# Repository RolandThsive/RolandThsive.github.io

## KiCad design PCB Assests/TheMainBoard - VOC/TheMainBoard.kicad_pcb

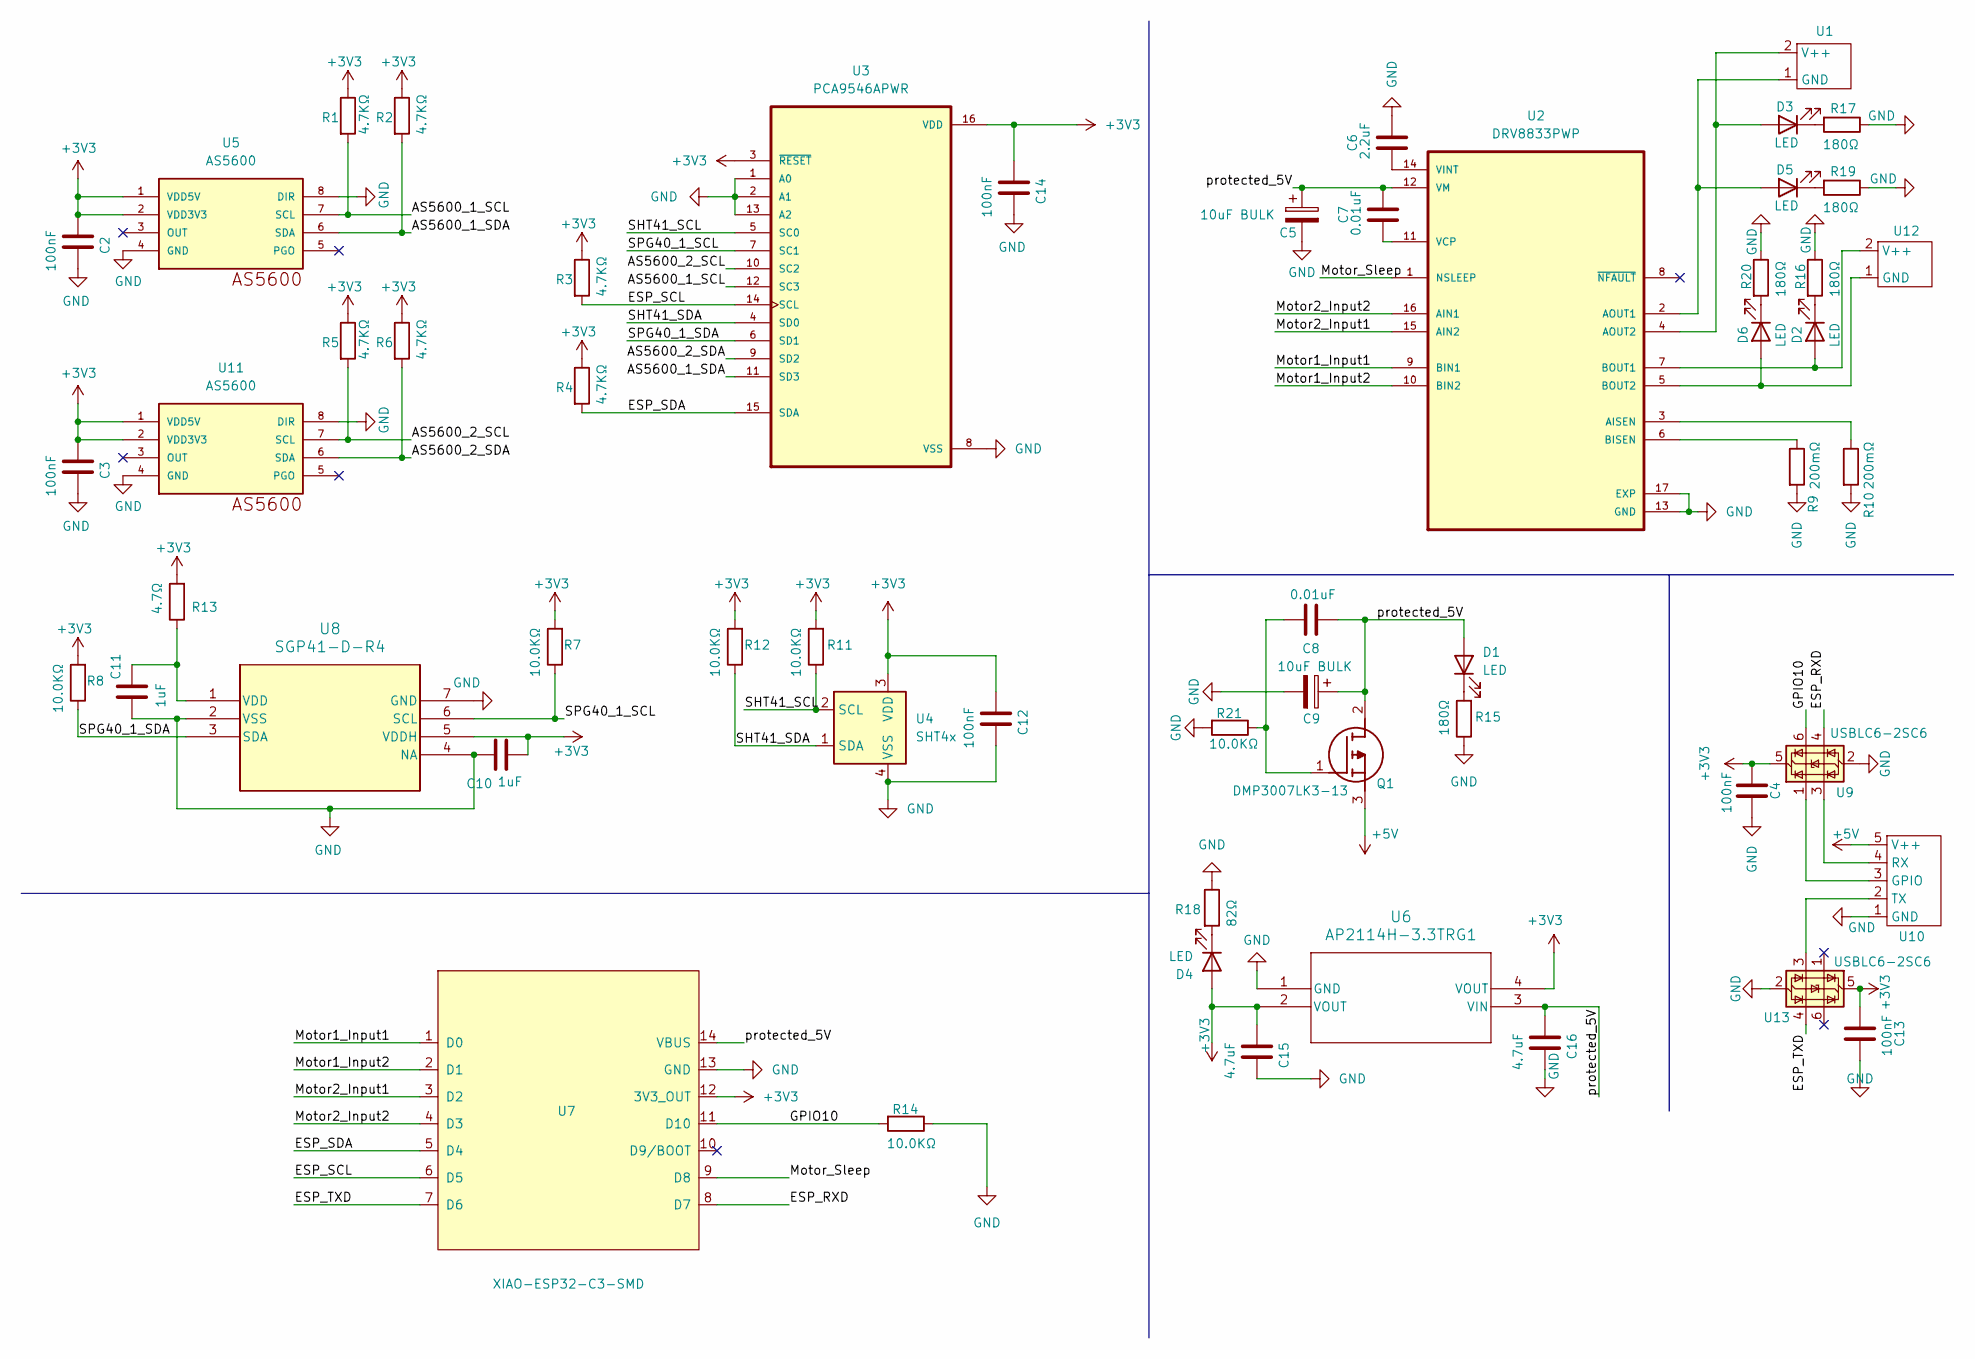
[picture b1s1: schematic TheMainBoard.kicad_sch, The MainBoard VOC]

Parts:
C2, C3, C4, C12, C13, C14: 100nF; C_0805_2012Metric_Pad1.18x1.45mm_HandSolder
C5, C9: 10uF BULK; CP_EIA-3528-21_Kemet-B_HandSolder
C6: 2.2uF; C_0805_2012Metric_Pad1.18x1.45mm_HandSolder
C7, C8: 0.01uF; C_0805_2012Metric_Pad1.18x1.45mm_HandSolder
C10, C11: 1uF; C_0805_2012Metric_Pad1.18x1.45mm_HandSolder
C15, C16: 4.7uF; C_0805_2012Metric_Pad1.18x1.45mm_HandSolder
D1, D2, D3, D4, D5, D6: LED; LED_1206_3216Metric
Q1: DMP3007LK3-13; DMP3007LK313; Manufacturer_Part_Number DMP3007LK3-13; Mouser Part Number 621-DMP3007LK3-13
R1, R2, R3, R4, R5, R6: 4.7KΩ; R_0805_2012Metric_Pad1.20x1.40mm_HandSolder
R7, R8, R11, R12, R14, R21: 10.0KΩ; R_0805_2012Metric_Pad1.20x1.40mm_HandSolder
R9, R10: 200mΩ; R_1206_3216Metric_Pad1.30x1.75mm_HandSolder
R13: 4.7Ω; R_0805_2012Metric_Pad1.20x1.40mm_HandSolder
R15, R16, R17, R19, R20: 180Ω; R_0805_2012Metric_Pad1.20x1.40mm_HandSolder
R18: 82Ω; R_0805_2012Metric_Pad1.20x1.40mm_HandSolder
U1, U12: 2PinsOut_foot
U2: DRV8833PWP; PW16_TEX; PARTREV E
U3: PCA9546APWR; SOP65P640X120-16N
U4: SHT4x; Sensirion_DFN-4_1.5x1.5mm_P0.8mm_SHT4x_NoCentralPad
U5, U11: AS5600; AS5600Alt
U6: AP2114H-3.3TRG1; SOT-223_DIO-L
U7: XIAO-ESP32-C3-SMD; XIAO-ESP32-C3-DIP
U8: SGP41-D-R4; SGP40_SEN-L
U9, U13: USBLC6-2SC6; SOT-23-6
U10: 5PinsOut_foot

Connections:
+3V3: C2.1, C3.1, C4.1, C10.2, C12.1, C13.1, C14.1, C15.1, D4.2 (A), R1.1, R2.1, R3.1, R4.1, R5.1, R6.1, R7.2, R8.2, R11.2, R12.2, R13.2, U3.3 (~RESET), U3.16 (VDD), U4.3 (VDD), U5.1 (VDD5V), U5.2 (VDD3V3), U6.2 (VOUT), U6.4 (VOUT), U7.12 (3V3_OUT), U8.5 (VDDH), U9.5 (VBUS), U11.1 (VDD5V), U11.2 (VDD3V3), U13.5 (VBUS)
+5V: Q1.3 (S), U10.5 (V++)
/AS5600_1_SCL: R1.2, U3.12 (SC3), U5.7 (SCL)
/AS5600_1_SDA: R2.2, U3.11 (SD3), U5.6 (SDA)
/AS5600_2_SCL: R5.2, U3.10 (SC2), U11.7 (SCL)
/AS5600_2_SDA: R6.2, U3.9 (SD2), U11.6 (SDA)
/ESP_RXD: U7.8 (D7), U9.4 (I/O2)
/ESP_SCL: R3.2, U3.14 (SCL), U7.6 (D5)
/ESP_SDA: R4.2, U3.15 (SDA), U7.5 (D4)
/ESP_TXD: U7.7 (D6), U13.4 (I/O2)
/GPIO10: R14.2, U7.11 (D10), U9.6 (I/O1)
/Motor1_Input1: U2.9 (BIN1), U7.1 (D0)
/Motor1_Input2: U2.10 (BIN2), U7.2 (D1)
/Motor2_Input1: U2.15 (AIN2), U7.3 (D2)
/Motor2_Input2: U2.16 (AIN1), U7.4 (D3)
/Motor_Sleep: U2.1 (NSLEEP), U7.9 (D8)
/SHT41_SCL: R11.1, U3.5 (SC0), U4.2 (SCL)
/SHT41_SDA: R12.1, U3.4 (SD0), U4.1 (SDA)
/SPG40_1_SCL: R7.1, U3.7 (SC1), U8.6 (SCL)
/SPG40_1_SDA: R8.1, U3.6 (SD1), U8.3 (SDA)
/protected_5V: C5.1, C7.2, C8.1, C9.1, C16.1, D1.2 (A), Q1.2 (D), U2.12 (VM), U6.3 (VIN), U7.14 (VBUS)
GND: C2.2, C3.2, C4.2, C5.2, C6.2, C9.2, C10.1, C11.2, C12.2, C13.2, C14.2, C15.2, C16.2, R9.2, R10.2, R14.1, R15.1, R16.1, R17.1, R18.1, R19.1, R20.1, R21.2, U2.13 (GND), U2.17 (EXP), U3.1 (A0), U3.2 (A1), U3.8 (VSS), U3.13 (A2), U4.4 (VSS), U5.4 (GND), U5.8 (DIR), U6.1 (GND), U7.13 (GND), U8.2 (VSS), U8.4 (NA), U8.7 (GND), U9.2 (GND), U10.1 (GND), U11.4 (GND), U11.8 (DIR), U13.2 (GND)
unnamed: D1.1 (K), R15.2
unnamed: D2.2 (A), U2.7 (BOUT1), U12.2 (V++)
unnamed: D2.1 (K), R16.2
unnamed: D3.2 (A), U1.2 (V++), U2.4 (AOUT2)
unnamed: D3.1 (K), R17.2
unnamed: D4.1 (K), R18.2
unnamed: D5.2 (A), U1.1 (GND), U2.2 (AOUT1)
unnamed: D5.1 (K), R19.2
unnamed: D6.2 (A), U2.5 (BOUT2), U12.1 (GND)
unnamed: D6.1 (K), R20.2
unnamed: C8.2, Q1.1 (G), R21.1
unnamed: R10.1, U2.3 (AISEN)
unnamed: R9.1, U2.6 (BISEN)
unnamed: C7.1, U2.11 (VCP)
unnamed: C6.1, U2.14 (VINT)
unnamed: C11.1, R13.1, U8.1 (VDD)
unnamed: U9.1 (I/O1), U10.3 (GPIO)
unnamed: U9.3 (I/O2), U10.4 (RX)
unnamed: U10.2 (TX), U13.3 (I/O2)

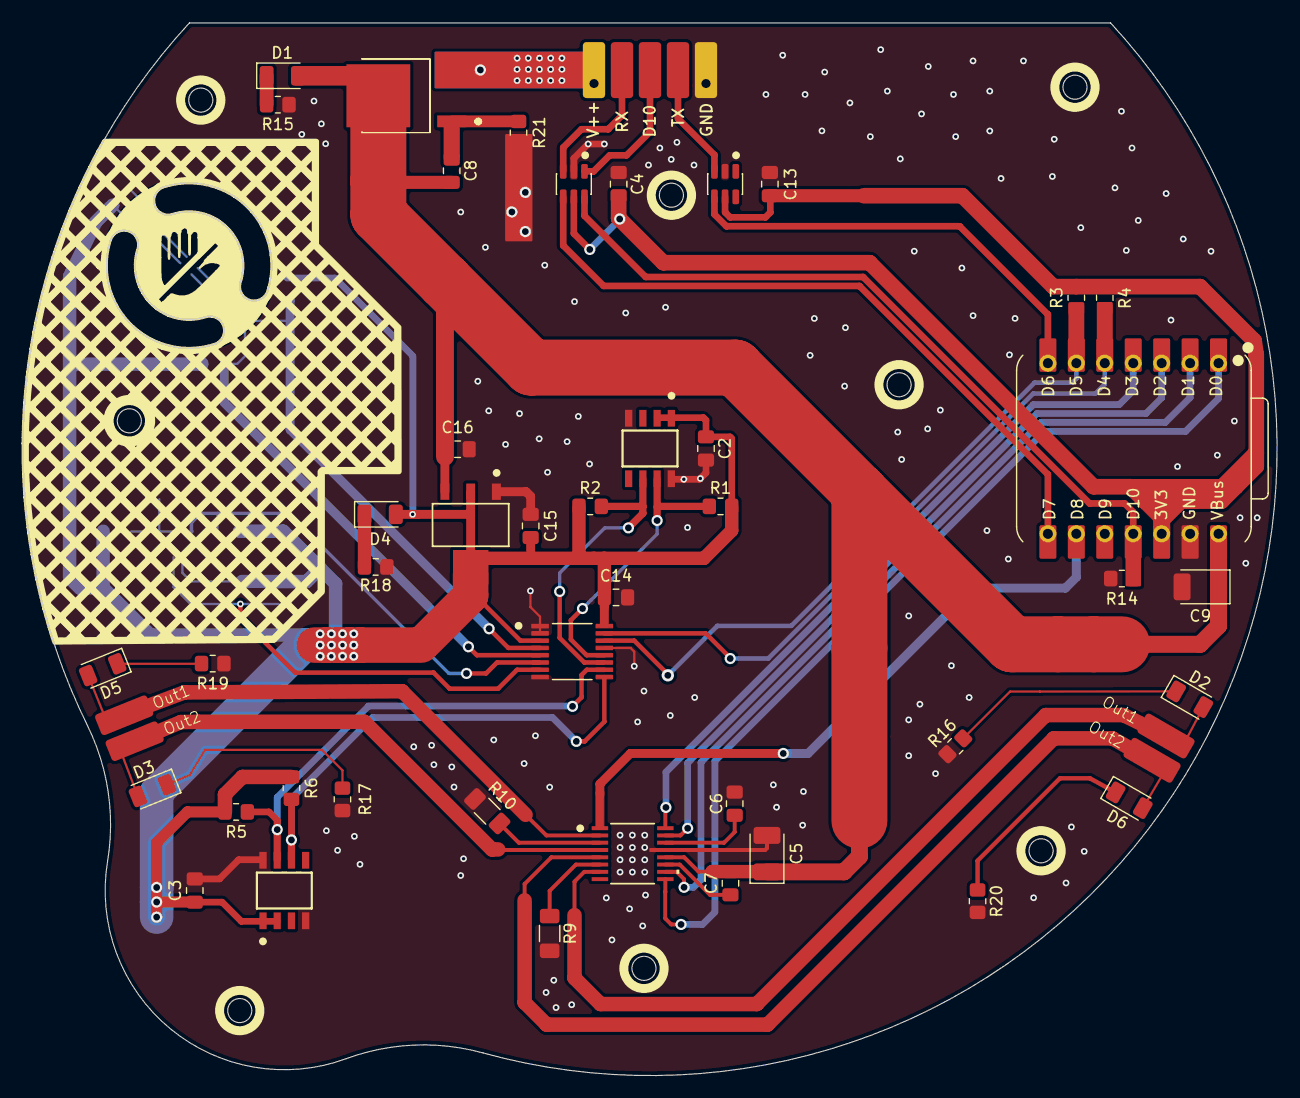
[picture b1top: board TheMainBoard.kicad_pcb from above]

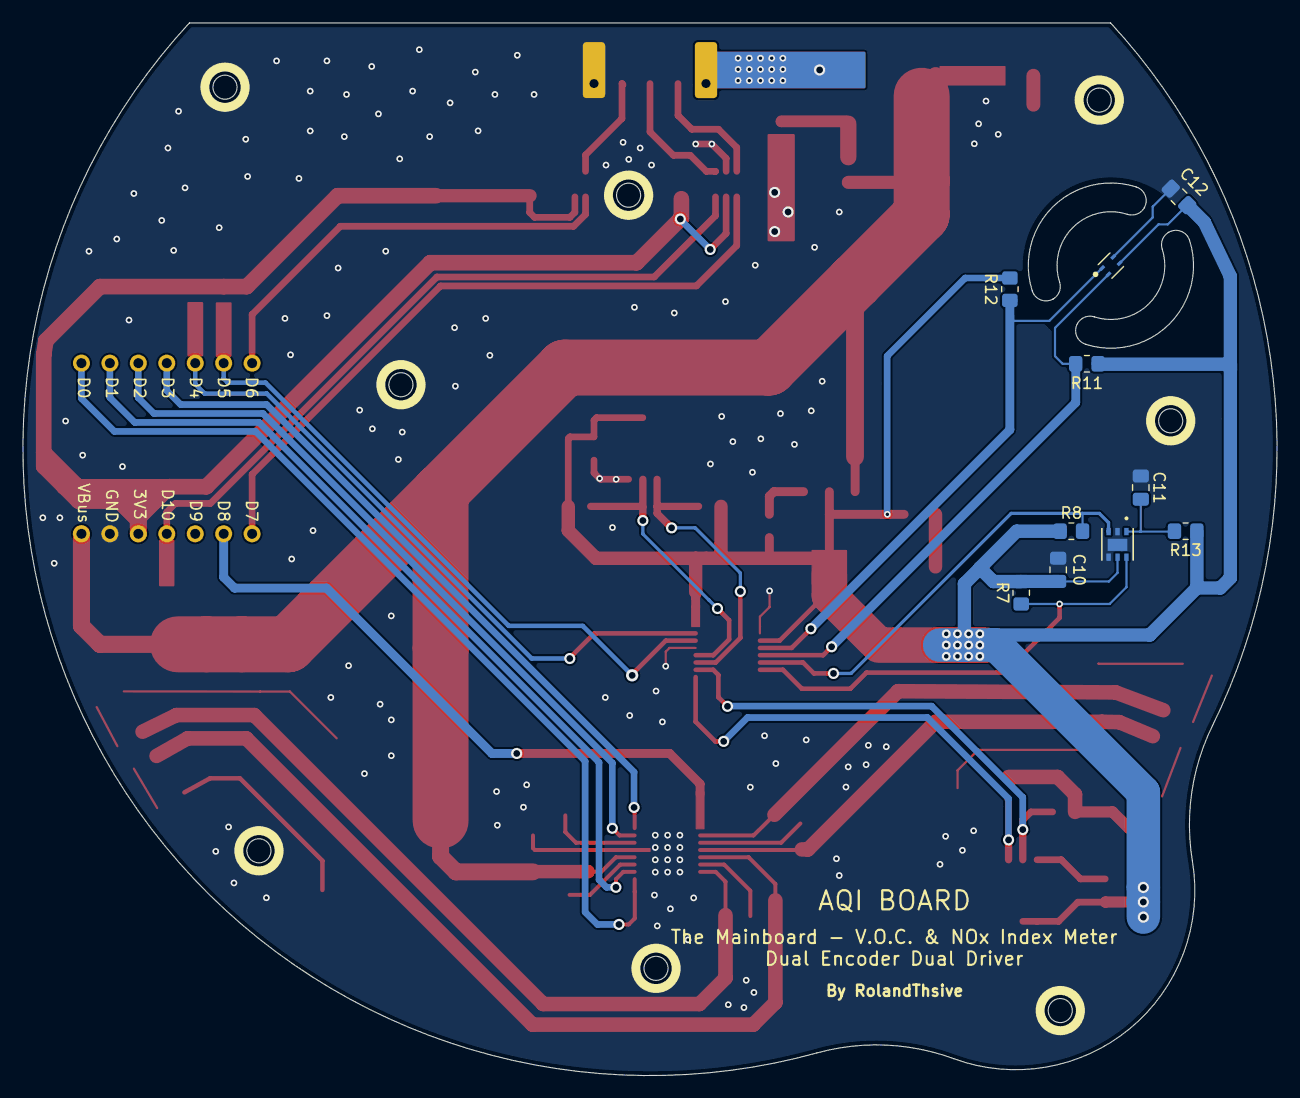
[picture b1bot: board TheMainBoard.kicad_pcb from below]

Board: 2 copper layers, 112.0 x 94.0 mm, 56 parts (10 on the bottom side), 41 nets.

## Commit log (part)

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2025-04-08 3D models Addition
2025-04-08 rename
2025-04-08 remove
2025-04-08 add posters
2025-04-09 All 3d Models
2025-04-09 404 page update
2025-04-09 images
2025-04-10 name changes
2025-04-11 The lower Assembly with circuits
2025-04-13 Three JS scripts added
2025-04-13 Updated js
2025-04-13 TNS ThreeJS update
2025-04-13 Update after update mn
2025-04-13 UPDATE BECAUSE I AM GOOD
2025-04-14 Update becasue Update
2025-04-15 Update baby update
2025-04-15 hoho update because I can do many things
2025-04-15 All functions work
2025-04-15 Chnaged colors
2025-04-15 new feature - toned down brightness for incandescnet
2025-04-15 minor update
2025-04-15 update n infinity
2025-04-15 update n infinity and beyond
2025-04-17 AuckVER2
2025-04-17 ANKVER
2025-04-17 update ackver poster
2025-04-17 up DA te
2025-04-17 Grove test
2025-08-31 Hand tool post
    Hand_tool_post _update
2025-08-31 Hand Tool post update
2025-08-31 hand_tool_motor_animated
2025-08-31 handtoolmotormovemnet
2025-08-31 handtool
2025-08-31 handtoolupdate
2025-08-31 motor_moving
2025-08-31 motor_mving _png
2025-09-01 top_hand_tool_expo
2025-09-01 modified
2025-09-01 with the stand
2025-09-01 poster - stand
2025-09-13 dampner
    Damper my man the correct spelling is damper not dampner
2025-09-13 hoho becasue
    no one hoho'ed more than me i am santa fr
2025-09-13 opent it uop
    Hell yeah
2025-09-15 animated_view
2025-09-15 full system of the dampner
2025-10-14 for_henry
2026-03-03 Create LICENSE
2026-03-22 Hercules for hercules
2026-03-22 GOJO is not hercules
2026-03-22 specially for the hercules robots
2026-03-22 ack new 640px
2026-03-22 new poster for the main stuff
2026-06-05 wrist assembly 3D model
2026-06-05 poster
2026-06-05 hygrometerCAD
2026-06-05 Poster for hygrometer
2026-06-05 facewithtickgearassem
2026-06-05 posterposterboy
2026-06-05 upup
2026-06-05 I am god of uploading
2026-06-05 upupuo
2026-06-05 pospos
2026-06-13 sfe exploded
2026-06-13 sfe stand
